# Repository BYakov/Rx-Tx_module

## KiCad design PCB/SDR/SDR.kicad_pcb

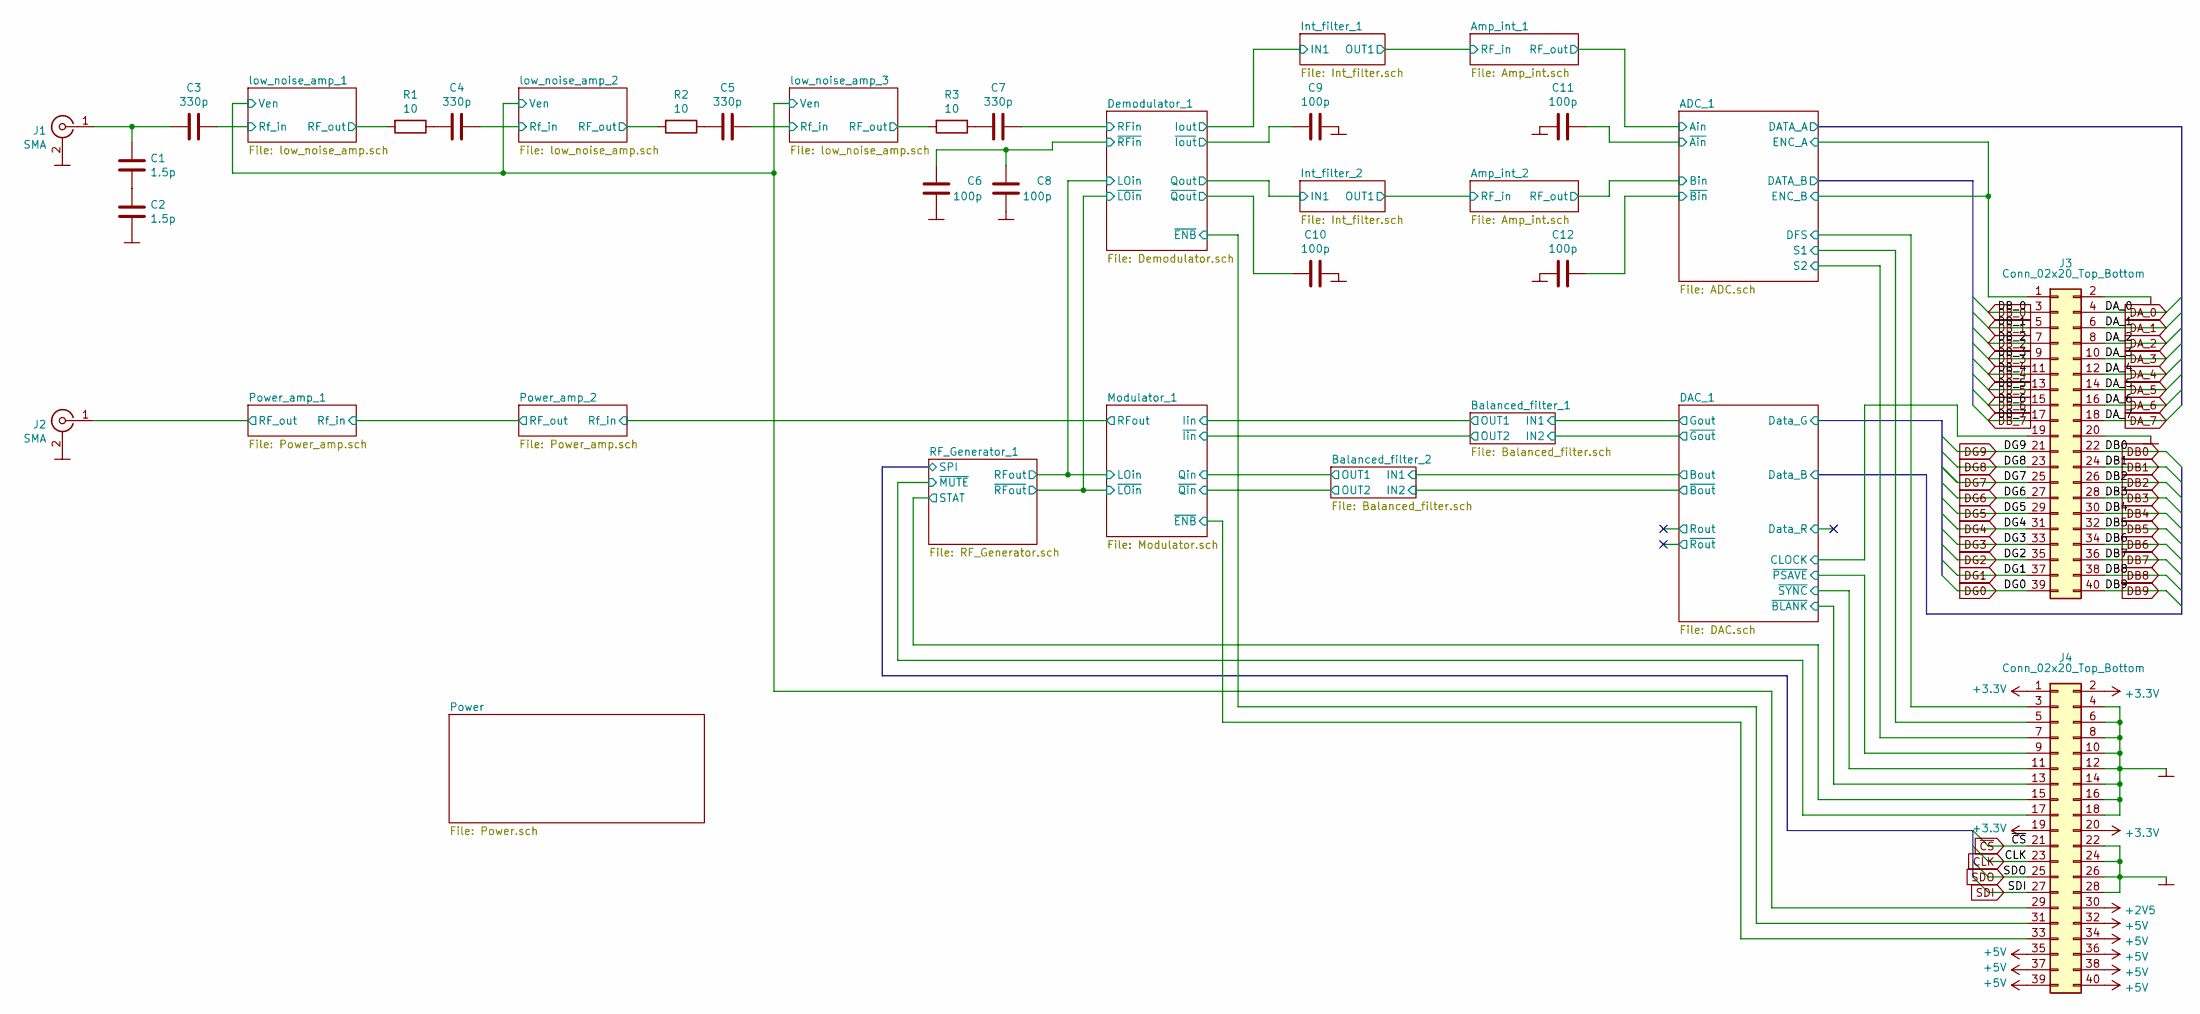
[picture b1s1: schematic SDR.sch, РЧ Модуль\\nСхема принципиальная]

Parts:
C1, C2: 1.5p; C_0805_2012Metric_Pad1.18x1.45mm_HandSolder
C3, C4, C5, C7: 330p; C_0805_2012Metric_Pad1.18x1.45mm_HandSolder
C6, C8, C9, C10, C11, C12: 100p; C_0805_2012Metric_Pad1.18x1.45mm_HandSolder
J1, J2: SMA; SMA_Amphenol_132289_EdgeMount
J3, J4: Conn_02x20_Top_Bottom; PinHeader_2x20_P2.54mm_Vertical
R1, R2, R3: 10; R_0805_2012Metric_Pad1.20x1.40mm_HandSolder

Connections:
+2V5: J4.30; also elsewhere on the board
+3V3: J4.1, J4.2, J4.19, J4.20; also elsewhere on the board
+5V: J4.32, J4.34, J4.35, J4.36, J4.37, J4.38, J4.39, J4.40; also elsewhere on the board
/ADC_1/DFS: J4.3; also elsewhere on the board
/ADC_1/ENC_A: J3.1; also elsewhere on the board
/ADC_1/S1: J4.5; also elsewhere on the board
/ADC_1/S2: J4.7; also elsewhere on the board
/ADC_1/~Ain: C12.2; also elsewhere on the board
/ADC_1/~Bin: C11.2; also elsewhere on the board
/DAC_1/CLOCK: J3.19; also elsewhere on the board
/DAC_1/~BLANK: J4.13; also elsewhere on the board
/DAC_1/~PSAVE: J4.9; also elsewhere on the board
/DAC_1/~SYNC: J4.11; also elsewhere on the board
/Demodulator_1/RFin: C7.1; also elsewhere on the board
/Demodulator_1/~ENB: J4.31; also elsewhere on the board
/Demodulator_1/~Iout: C9.1; also elsewhere on the board
/Demodulator_1/~Qout: C10.1; also elsewhere on the board
/Demodulator_1/~RFin: C6.2, C8.2; also elsewhere on the board
/Modulator_1/~ENB: J4.33; also elsewhere on the board
/Power_amp_1/RF_out: J2.1 (In); also elsewhere on the board
/RF_Generator_1/STAT: J4.15; also elsewhere on the board
/RF_Generator_1/~MUTE: J4.17; also elsewhere on the board
/low_noise_amp_1/RF_out: R1.2; also elsewhere on the board
/low_noise_amp_1/Rf_in: C3.1; also elsewhere on the board
/low_noise_amp_1/Ven: J4.29; also elsewhere on the board
/low_noise_amp_2/RF_out: R2.2; also elsewhere on the board
/low_noise_amp_2/Rf_in: C4.1; also elsewhere on the board
/low_noise_amp_3/RF_out: R3.2; also elsewhere on the board
/low_noise_amp_3/Rf_in: C5.1; also elsewhere on the board
CLK: J4.23; also elsewhere on the board
COMM: C2.2, C6.1, C8.1, C9.2, C10.2, C11.1, C12.1, J1.2 (Ext), J2.2 (Ext), J3.2, J3.20, J4.4, J4.6, J4.8, J4.10, J4.12, J4.14, J4.16, J4.18, J4.22, J4.24, J4.26, J4.28; also elsewhere on the board
DA_0: J3.4; also elsewhere on the board
DA_1: J3.6; also elsewhere on the board
DA_2: J3.8; also elsewhere on the board
DA_3: J3.10; also elsewhere on the board
DA_4: J3.12; also elsewhere on the board
DA_5: J3.14; also elsewhere on the board
DA_6: J3.16; also elsewhere on the board
DA_7: J3.18; also elsewhere on the board
DB0: J3.22; also elsewhere on the board
DB1: J3.24; also elsewhere on the board
DB2: J3.26; also elsewhere on the board
DB3: J3.28; also elsewhere on the board
DB4: J3.30; also elsewhere on the board
DB5: J3.32; also elsewhere on the board
DB6: J3.34; also elsewhere on the board
DB7: J3.36; also elsewhere on the board
DB8: J3.38; also elsewhere on the board
DB9: J3.40; also elsewhere on the board
DB_0: J3.3; also elsewhere on the board
DB_1: J3.5; also elsewhere on the board
DB_2: J3.7; also elsewhere on the board
DB_3: J3.9; also elsewhere on the board
DB_4: J3.11; also elsewhere on the board
DB_5: J3.13; also elsewhere on the board
DB_6: J3.15; also elsewhere on the board
DB_7: J3.17; also elsewhere on the board
DG0: J3.39; also elsewhere on the board
DG1: J3.37; also elsewhere on the board
DG2: J3.35; also elsewhere on the board
DG3: J3.33; also elsewhere on the board
DG4: J3.31; also elsewhere on the board
DG5: J3.29; also elsewhere on the board
DG6: J3.27; also elsewhere on the board
DG7: J3.25; also elsewhere on the board
DG8: J3.23; also elsewhere on the board
DG9: J3.21; also elsewhere on the board
unnamed: C1.1, C3.2, J1.1 (In)
unnamed: C1.2, C2.1
unnamed: C4.2, R1.1
unnamed: C5.2, R2.1
unnamed: C7.2, R3.1
SDI: J4.27; also elsewhere on the board
SDO: J4.25; also elsewhere on the board
~CS: J4.21; also elsewhere on the board

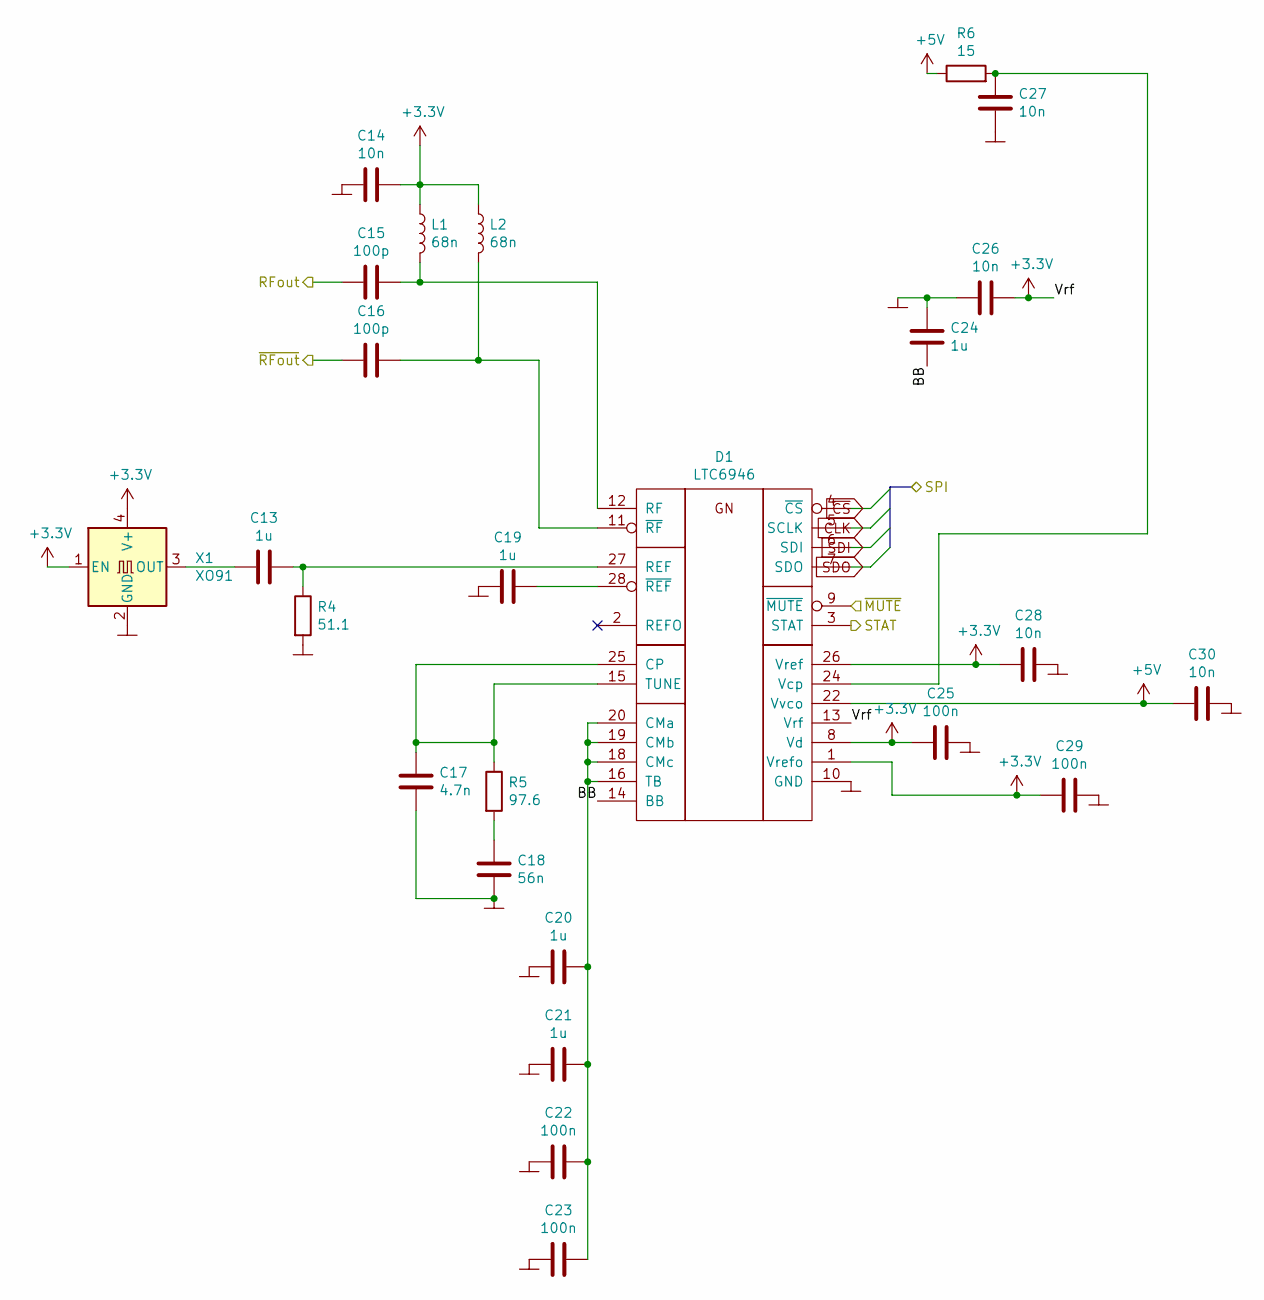
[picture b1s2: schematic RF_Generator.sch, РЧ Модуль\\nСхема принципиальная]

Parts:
C13, C19, C20, C21, C24: 1u; C_0805_2012Metric_Pad1.18x1.45mm_HandSolder
C14, C26, C27, C28, C30: 10n; C_1206_3216Metric_Pad1.33x1.80mm_HandSolder
C15, C16: 100p; C_0805_2012Metric_Pad1.18x1.45mm_HandSolder
C17: 4.7n; C_1206_3216Metric_Pad1.33x1.80mm_HandSolder
C18: 56n; C_1206_3216Metric_Pad1.33x1.80mm_HandSolder
C22, C23, C25, C29: 100n; C_1206_3216Metric_Pad1.33x1.80mm_HandSolder
D1: LTC6946; QFN-28-1EP_4x5mm_P0.5mm_EP2.65x3.65mm_ThermalVias
L1, L2: 68n; L_0402_1005Metric_Pad0.77x0.64mm_HandSolder
R4: 51.1; R_0805_2012Metric_Pad1.20x1.40mm_HandSolder
R5: 97.6; R_0805_2012Metric_Pad1.20x1.40mm_HandSolder
R6: 15; R_0805_2012Metric_Pad1.20x1.40mm_HandSolder
X1: XO91; Oscillator_SMD_EuroQuartz_XO91-4Pin_7.0x5.0mm

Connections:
+3V3: C14.1, C25.1, C26.1, C28.1, C29.1, D1.1 (Vrefo), D1.8 (Vd), D1.13 (Vrf), D1.26 (Vref), L1.1, L2.1, X1.1 (EN), X1.4 (V+); also elsewhere on the board
+5V: C30.1, D1.22 (Vvco), R6.1; also elsewhere on the board
/Demodulator_1/LOin: C15.2; also elsewhere on the board
/Demodulator_1/~LOin: C16.2; also elsewhere on the board
/RF_Generator_1/BB: C24.2, D1.14 (BB)
/RF_Generator_1/STAT: D1.3 (STAT); also elsewhere on the board
/RF_Generator_1/~MUTE: D1.9 (~MUTE); also elsewhere on the board
CLK: D1.5 (SCLK); also elsewhere on the board
COMM: C14.2, C17.2, C18.2, C19.1, C20.2, C21.2, C22.2, C23.2, C24.1, C25.2, C26.2, C27.2, C28.2, C29.2, C30.2, D1.10 (GND), D1.17 (GND), D1.21 (GND), D1.23 (GND), D1.29 (Ep), R4.2, X1.2 (GND); also elsewhere on the board
unnamed: C13.1, D1.27 (REF), R4.1
unnamed: C13.2, X1.3 (OUT)
unnamed: C15.1, D1.12 (RF), L1.2
unnamed: C16.1, D1.11 (~RF), L2.2
unnamed: C17.1, D1.15 (TUNE), D1.25 (CP), R5.1
unnamed: C18.1, R5.2
unnamed: C19.2, D1.28 (~REF)
unnamed: C20.1, C21.1, C22.1, C23.1, D1.16 (TB), D1.18 (CMc), D1.19 (CMb), D1.20 (CMa)
unnamed: C27.1, D1.24 (Vcp), R6.2
SDI: D1.6 (SDI); also elsewhere on the board
SDO: D1.7 (SDO); also elsewhere on the board
~CS: D1.4 (~CS); also elsewhere on the board

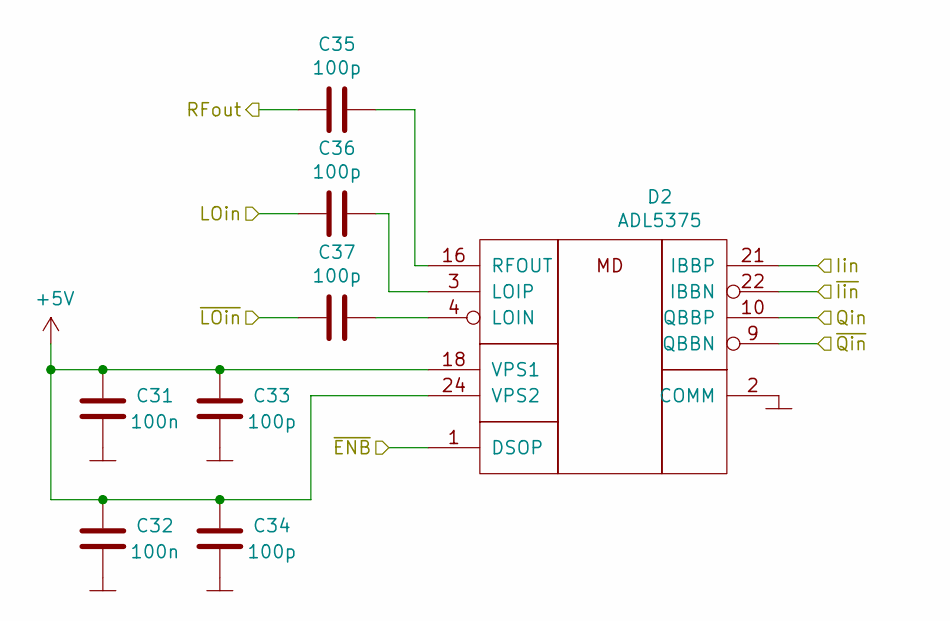
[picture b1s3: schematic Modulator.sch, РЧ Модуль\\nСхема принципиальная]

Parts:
C31, C32: 100n; C_1206_3216Metric_Pad1.33x1.80mm_HandSolder
C33, C34, C35, C36, C37: 100p; C_0805_2012Metric_Pad1.18x1.45mm_HandSolder
D2: ADL5375; LFCSP-24-1EP_4x4mm_P0.5mm_EP2.5x2.5mm_ThermalVias

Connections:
+5V: C31.2, C32.2, C33.2, C34.2, D2.18 (VPS1), D2.24 (VPS2); also elsewhere on the board
/Balanced_filter_1/OUT2: D2.22 (IBBN); also elsewhere on the board
/Balanced_filter_2/OUT1: D2.10 (QBBP); also elsewhere on the board
/Balanced_filter_2/OUT2: D2.9 (QBBN); also elsewhere on the board
/Demodulator_1/LOin: C36.2; also elsewhere on the board
/Demodulator_1/~LOin: C37.2; also elsewhere on the board
/Modulator_1/Iin: D2.21 (IBBP); also elsewhere on the board
/Modulator_1/RFout: C35.1; also elsewhere on the board
/Modulator_1/~ENB: D2.1 (DSOP); also elsewhere on the board
COMM: C31.1, C32.1, C33.1, C34.1, D2.2 (COMM), D2.5 (COMM), D2.8 (COMM), D2.11 (COMM), D2.12 (COMM), D2.14 (COMM), D2.17 (COMM), D2.19 (COMM), D2.20 (COMM), D2.23 (COMM), D2.25 (EP); also elsewhere on the board
unnamed: C35.2, D2.16 (RFOUT)
unnamed: C36.1, D2.3 (LOIP)
unnamed: C37.1, D2.4 (LOIN)

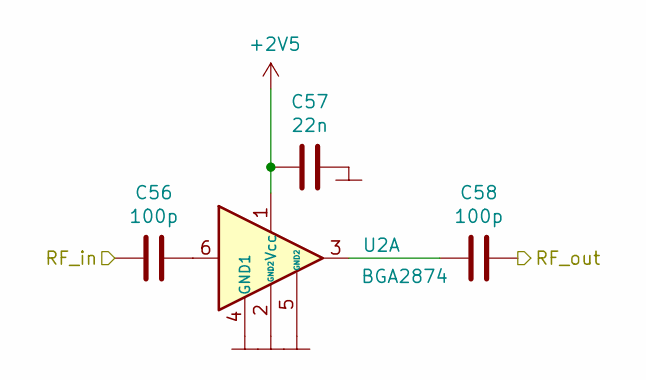
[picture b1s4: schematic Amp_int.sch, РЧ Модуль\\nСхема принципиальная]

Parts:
C38, C40: 100p; C_0805_2012Metric_Pad1.18x1.45mm_HandSolder
C39: 22n; C_0805_2012Metric_Pad1.18x1.45mm_HandSolder
U1: BGA2874; SOT-363_SC-70-6_Handsoldering

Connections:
+2V5: C39.2, U1.1 (Vcc); also elsewhere on the board
/ADC_1/Bin: C40.1; also elsewhere on the board
/Int_filter_1/OUT1: C38.2; also elsewhere on the board
COMM: C39.1, U1.2 (GND2), U1.4 (GND1), U1.5 (GND2); also elsewhere on the board
unnamed: C38.1, U1.6
unnamed: C40.2, U1.3

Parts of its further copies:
C56, C58: 100p; C_0805_2012Metric_Pad1.18x1.45mm_HandSolder
C57: 22n; C_0805_2012Metric_Pad1.18x1.45mm_HandSolder
U2: BGA2874; SOT-363_SC-70-6_Handsoldering

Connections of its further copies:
+2V5: C57.2, U2.1 (Vcc); also elsewhere on the board
/ADC_1/Ain: C58.1; also elsewhere on the board
/Int_filter_2/OUT1: C56.2; also elsewhere on the board
COMM: C57.1, U2.2 (GND2), U2.4 (GND1), U2.5 (GND2); also elsewhere on the board
unnamed: C56.1, U2.6
unnamed: C58.2, U2.3

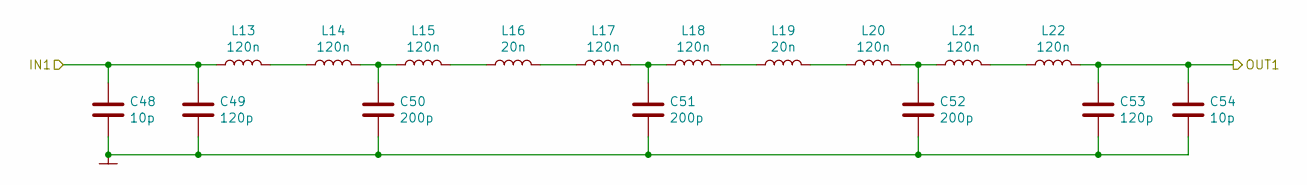
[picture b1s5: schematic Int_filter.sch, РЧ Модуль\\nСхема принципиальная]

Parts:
C41, C47: 10p; C_0805_2012Metric_Pad1.18x1.45mm_HandSolder
C42, C46: 120p; C_0805_2012Metric_Pad1.18x1.45mm_HandSolder
C43, C44, C45: 200p; C_0805_2012Metric_Pad1.18x1.45mm_HandSolder
L3, L4, L5, L7, L8, L10, L11, L12: 120n; L_0402_1005Metric_Pad0.77x0.64mm_HandSolder
L6, L9: 20n; L_0603_1608Metric_Pad1.05x0.95mm_HandSolder

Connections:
/Int_filter_1/IN1: C41.1, C42.1, L3.1; also elsewhere on the board
/Int_filter_1/OUT1: C46.1, C47.1, L12.2; also elsewhere on the board
COMM: C41.2, C42.2, C43.2, C44.2, C45.2, C46.2, C47.2; also elsewhere on the board
unnamed: C43.1, L4.2, L5.1
unnamed: C44.1, L7.2, L8.1
unnamed: C45.1, L10.2, L11.1
unnamed: L3.2, L4.1
unnamed: L5.2, L6.1
unnamed: L6.2, L7.1
unnamed: L8.2, L9.1
unnamed: L9.2, L10.1
unnamed: L11.2, L12.1

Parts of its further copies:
C48, C54: 10p; C_0805_2012Metric_Pad1.18x1.45mm_HandSolder
C49, C53: 120p; C_0805_2012Metric_Pad1.18x1.45mm_HandSolder
C50, C51, C52: 200p; C_0805_2012Metric_Pad1.18x1.45mm_HandSolder
L13, L14, L15, L17, L18, L20, L21, L22: 120n; L_0402_1005Metric_Pad0.77x0.64mm_HandSolder
L16, L19: 20n; L_0603_1608Metric_Pad1.05x0.95mm_HandSolder

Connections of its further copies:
/Int_filter_2/IN1: C48.1, C49.1, L13.1; also elsewhere on the board
/Int_filter_2/OUT1: C53.1, C54.1, L22.2; also elsewhere on the board
COMM: C48.2, C49.2, C50.2, C51.2, C52.2, C53.2, C54.2; also elsewhere on the board
unnamed: C50.1, L14.2, L15.1
unnamed: C51.1, L17.2, L18.1
unnamed: C52.1, L20.2, L21.1
unnamed: L13.2, L14.1
unnamed: L15.2, L16.1
unnamed: L16.2, L17.1
unnamed: L18.2, L19.1
unnamed: L19.2, L20.1
unnamed: L21.2, L22.1

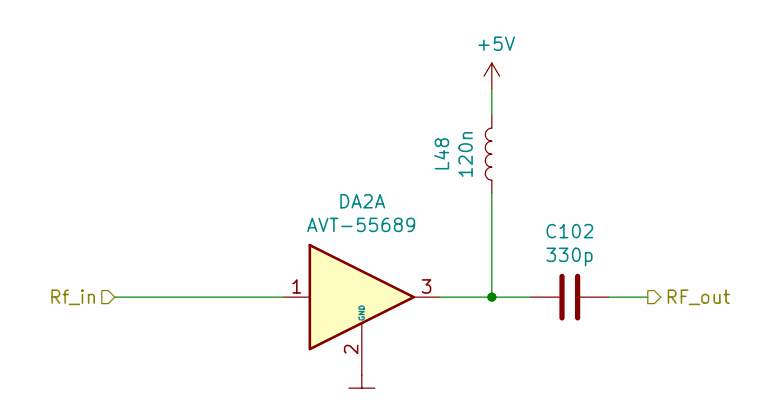
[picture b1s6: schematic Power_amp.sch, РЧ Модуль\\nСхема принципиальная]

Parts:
C55: 330p; C_1206_3216Metric_Pad1.33x1.80mm_HandSolder
DA1: AVT-55689; SOT-89-3_Handsoldering
L23: 120n; L_0402_1005Metric_Pad0.77x0.64mm_HandSolder

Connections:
+5V: L23.2; also elsewhere on the board
/Power_amp_1/RF_out: C55.1; also elsewhere on the board
/Power_amp_2/RF_out: DA1.1; also elsewhere on the board
COMM: DA1.2 (GND); also elsewhere on the board
unnamed: C55.2, DA1.3, L23.1

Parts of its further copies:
C102: 330p; C_1206_3216Metric_Pad1.33x1.80mm_HandSolder
DA2: AVT-55689; SOT-89-3_Handsoldering
L48: 120n; L_0402_1005Metric_Pad0.77x0.64mm_HandSolder

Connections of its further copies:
+5V: L48.2; also elsewhere on the board
/Modulator_1/RFout: DA2.1; also elsewhere on the board
/Power_amp_2/RF_out: C102.1; also elsewhere on the board
COMM: DA2.2 (GND); also elsewhere on the board
unnamed: C102.2, DA2.3, L48.1

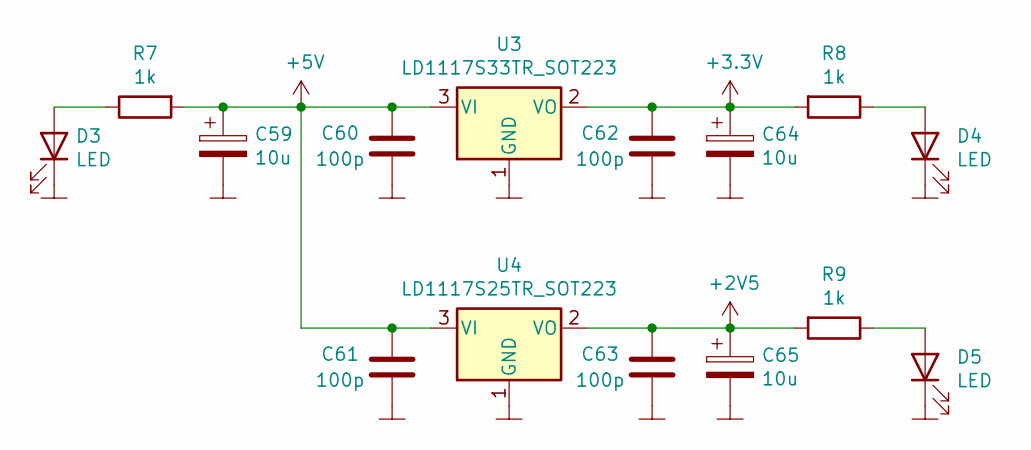
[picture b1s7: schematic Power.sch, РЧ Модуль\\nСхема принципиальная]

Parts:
C59, C64, C65: 10u; CP_Elec_4x5.4
C60, C61, C62, C63: 100p; C_0805_2012Metric_Pad1.18x1.45mm_HandSolder
D3, D4, D5: LED; D_1206_3216Metric_Pad1.42x1.75mm_HandSolder
R7, R8, R9: 1k; R_0805_2012Metric_Pad1.20x1.40mm_HandSolder
U3: LD1117S33TR_SOT223; SOT-223-3_TabPin2
U4: LD1117S25TR_SOT223; SOT-223-3_TabPin2

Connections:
+2V5: C63.2, C65.1, R9.2, U4.2 (VO); also elsewhere on the board
+3V3: C62.2, C64.1, R8.2, U3.2 (VO); also elsewhere on the board
+5V: C59.1, C60.2, C61.2, R7.2, U3.3 (VI), U4.3 (VI); also elsewhere on the board
COMM: C59.2, C60.1, C61.1, C62.1, C63.1, C64.2, C65.2, D3.1 (K), D4.1 (K), D5.1 (K), U3.1 (GND), U4.1 (GND); also elsewhere on the board
unnamed: D3.2 (A), R7.1
unnamed: D4.2 (A), R8.1
unnamed: D5.2 (A), R9.1

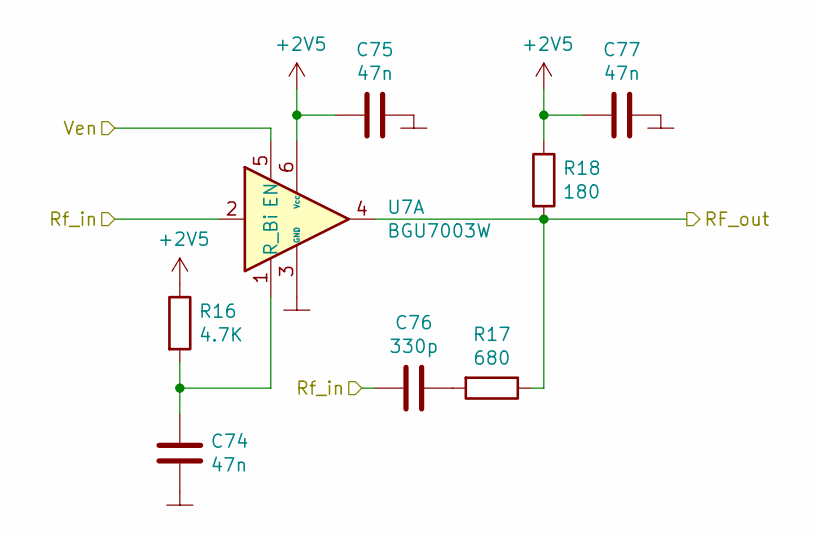
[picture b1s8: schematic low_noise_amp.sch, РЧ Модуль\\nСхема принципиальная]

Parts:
C66, C67, C69: 47n; C_1206_3216Metric_Pad1.33x1.80mm_HandSolder
C68: 330p; C_0805_2012Metric_Pad1.18x1.45mm_HandSolder
R10: 4.7К; R_0805_2012Metric_Pad1.20x1.40mm_HandSolder
R11: 680; R_0805_2012Metric_Pad1.20x1.40mm_HandSolder
R12: 180; R_0805_2012Metric_Pad1.20x1.40mm_HandSolder
U5: BGU7003W; SOT-886

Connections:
+2V5: C67.2, C69.2, R10.1, R12.1, U5.6 (Vcc); also elsewhere on the board
/low_noise_amp_1/RF_out: R11.1, R12.2, U5.4; also elsewhere on the board
/low_noise_amp_1/Rf_in: C68.2, U5.2; also elsewhere on the board
/low_noise_amp_1/Ven: U5.5 (EN); also elsewhere on the board
COMM: C66.2, C67.1, C69.1, U5.3 (GND); also elsewhere on the board
unnamed: C66.1, R10.2, U5.1 (R_Bi)
unnamed: C68.1, R11.2

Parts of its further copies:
C70, C71, C73, C74, C75, C77: 47n; C_1206_3216Metric_Pad1.33x1.80mm_HandSolder
C72, C76: 330p; C_0805_2012Metric_Pad1.18x1.45mm_HandSolder
R13, R16: 4.7К; R_0805_2012Metric_Pad1.20x1.40mm_HandSolder
R14, R17: 680; R_0805_2012Metric_Pad1.20x1.40mm_HandSolder
R15, R18: 180; R_0805_2012Metric_Pad1.20x1.40mm_HandSolder
U6, U7: BGU7003W; SOT-886

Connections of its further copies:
+2V5: C71.2, C73.2, C75.2, C77.2, R13.1, R15.1, R16.1, R18.1, U6.6 (Vcc), U7.6 (Vcc); also elsewhere on the board
/low_noise_amp_1/Ven: U6.5 (EN), U7.5 (EN); also elsewhere on the board
/low_noise_amp_2/RF_out: R14.1, R15.2, U6.4; also elsewhere on the board
/low_noise_amp_2/Rf_in: C72.2, U6.2; also elsewhere on the board
/low_noise_amp_3/RF_out: R17.1, R18.2, U7.4; also elsewhere on the board
/low_noise_amp_3/Rf_in: C76.2, U7.2; also elsewhere on the board
COMM: C70.2, C71.1, C73.1, C74.2, C75.1, C77.1, U6.3 (GND), U7.3 (GND); also elsewhere on the board
unnamed: C70.1, R13.2, U6.1 (R_Bi)
unnamed: C72.1, R14.2
unnamed: C74.1, R16.2, U7.1 (R_Bi)
unnamed: C76.1, R17.2

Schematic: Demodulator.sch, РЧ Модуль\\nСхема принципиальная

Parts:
C78, C79, C80: 100n; C_1206_3216Metric_Pad1.33x1.80mm_HandSolder
C81, C82, C83: 100p; C_0805_2012Metric_Pad1.18x1.45mm_HandSolder
D6: ADL5380; LFCSP-24-1EP_4x4mm_P0.5mm_EP2.5x2.5mm_ThermalVias
R19: R; R_0805_2012Metric_Pad1.20x1.40mm_HandSolder

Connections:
+5V: C78.2, C79.2, C80.2, C81.2, C82.2, C83.2, D6.6 (VCC1), D6.13 (VCC2), D6.24 (VCC3), R19.2; also elsewhere on the board
/Demodulator_1/LOin: D6.9 (LOIP); also elsewhere on the board
/Demodulator_1/RFin: D6.22 (RFIP); also elsewhere on the board
/Demodulator_1/~ENB: D6.7 (ENBL); also elsewhere on the board
/Demodulator_1/~Iout: D6.4 (ILO); also elsewhere on the board
/Demodulator_1/~LOin: D6.10 (LOIN); also elsewhere on the board
/Demodulator_1/~Qout: D6.16 (QLO); also elsewhere on the board
/Demodulator_1/~RFin: D6.21 (RFIN); also elsewhere on the board
/Int_filter_1/IN1: D6.3 (IHI); also elsewhere on the board
/Int_filter_2/IN1: D6.15 (QHI); also elsewhere on the board
COMM: C78.1, C79.1, C80.1, C81.1, C82.1, C83.1, D6.1 (GND3), D6.2 (GND1), D6.5 (GND1), D6.8 (GND4), D6.11 (GND4), D6.14 (GND2), D6.17 (GND2), D6.18 (GND3), D6.20 (GND3), D6.23 (GND3), D6.25 (EP); also elsewhere on the board
unnamed: D6.19 (ADJ), R19.1

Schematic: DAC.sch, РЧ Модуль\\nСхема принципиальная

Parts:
C84: 1u; C_1206_3216Metric_Pad1.33x1.80mm_HandSolder
C85, C86, C87: 100n; C_1206_3216Metric_Pad1.33x1.80mm_HandSolder
D7: ADV7123; LQFP-48_7x7mm_P0.5mm
D8: D_Zener; SOT-23
R20: R; R_0805_2012Metric_Pad1.20x1.40mm_HandSolder
R21: 1.5k; R_0805_2012Metric_Pad1.20x1.40mm_HandSolder

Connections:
+3V3: C85.1, C86.2, C87.1, D7.13 (VAA), D7.29 (VAA), D7.30 (VAA), R21.1; also elsewhere on the board
/Balanced_filter_1/IN2: D7.31 (~IOG); also elsewhere on the board
/Balanced_filter_2/IN2: D7.27 (~IOB); also elsewhere on the board
/DAC_1/Bout: D7.28 (IOB); also elsewhere on the board
/DAC_1/CLOCK: D7.24 (CLOCK); also elsewhere on the board
/DAC_1/DR0: D7.39 (R0)
/DAC_1/DR1: D7.40 (R1)
/DAC_1/DR2: D7.41 (R2)
/DAC_1/DR3: D7.42 (R3)
/DAC_1/DR4: D7.43 (R4)
/DAC_1/DR5: D7.44 (R5)
/DAC_1/DR6: D7.45 (R6)
/DAC_1/DR7: D7.46 (R7)
/DAC_1/DR8: D7.47 (R8)
/DAC_1/DR9: D7.48 (R9)
/DAC_1/Gout: D7.32 (IOG); also elsewhere on the board
/DAC_1/Rout: D7.34 (IOR)
/DAC_1/~BLANK: D7.11 (~BLANK); also elsewhere on the board
/DAC_1/~PSAVE: D7.38 (~PSAVE); also elsewhere on the board
/DAC_1/~Rout: D7.33 (~IOR)
/DAC_1/~SYNC: D7.12 (~SYNC); also elsewhere on the board
COMM: C84.2, C85.2, C87.2, D7.25 (GND), D7.26 (GND), D8.2 (A), R20.2; also elsewhere on the board
DB0: D7.14 (B0); also elsewhere on the board
DB1: D7.15 (B1); also elsewhere on the board
DB2: D7.16 (B2); also elsewhere on the board
DB3: D7.17 (B3); also elsewhere on the board
DB4: D7.18 (B4); also elsewhere on the board
DB5: D7.19 (B5); also elsewhere on the board
DB6: D7.20 (B6); also elsewhere on the board
DB7: D7.21 (B7); also elsewhere on the board
DB8: D7.22 (B8); also elsewhere on the board
DB9: D7.23 (B9); also elsewhere on the board
DG0: D7.1 (G0); also elsewhere on the board
DG1: D7.2 (G1); also elsewhere on the board
DG2: D7.3 (G2); also elsewhere on the board
DG3: D7.4 (G3); also elsewhere on the board
DG4: D7.5 (G4); also elsewhere on the board
DG5: D7.6 (G5); also elsewhere on the board
DG6: D7.7 (G6); also elsewhere on the board
DG7: D7.8 (G7); also elsewhere on the board
DG8: D7.9 (G8); also elsewhere on the board
DG9: D7.10 (G9); also elsewhere on the board
unnamed: C84.1, D7.36 (Vref), D8.1 (K), R21.2
unnamed: C86.1, D7.35 (COMP)
unnamed: D7.37 (Rset), R20.1

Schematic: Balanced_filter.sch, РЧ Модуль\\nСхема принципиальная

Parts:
C88, C94: 10p; C_0805_2012Metric_Pad1.18x1.45mm_HandSolder
C89, C93: 120p; C_0805_2012Metric_Pad1.18x1.45mm_HandSolder
C90, C91, C92: 200p; C_0805_2012Metric_Pad1.18x1.45mm_HandSolder
L24, L25, L26, L27, L32, L33, L34, L35: 120n; L_0402_1005Metric_Pad0.77x0.64mm_HandSolder
L28, L29, L30, L31: 10n; L_0402_1005Metric_Pad0.77x0.64mm_HandSolder

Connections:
/Balanced_filter_1/IN2: C88.2, C89.2, L25.1; also elsewhere on the board
/Balanced_filter_1/OUT2: C93.2, C94.2, L35.2; also elsewhere on the board
/DAC_1/Gout: C88.1, C89.1, L24.1; also elsewhere on the board
/Modulator_1/Iin: C93.1, C94.1, L34.2; also elsewhere on the board
unnamed: C90.1, L24.2, L26.1
unnamed: C90.2, L25.2, L27.1
unnamed: C91.1, L28.2, L30.1
unnamed: C91.2, L29.2, L31.1
unnamed: C92.1, L32.2, L34.1
unnamed: C92.2, L33.2, L35.1
unnamed: L26.2, L28.1
unnamed: L27.2, L29.1
unnamed: L30.2, L32.1
unnamed: L31.2, L33.1

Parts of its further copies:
C95, C101: 10p; C_0805_2012Metric_Pad1.18x1.45mm_HandSolder
C96, C100: 120p; C_0805_2012Metric_Pad1.18x1.45mm_HandSolder
C97, C98, C99: 200p; C_0805_2012Metric_Pad1.18x1.45mm_HandSolder
L36, L37, L38, L39, L44, L45, L46, L47: 120n; L_0402_1005Metric_Pad0.77x0.64mm_HandSolder
L40, L41, L42, L43: 10n; L_0402_1005Metric_Pad0.77x0.64mm_HandSolder

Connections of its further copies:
/Balanced_filter_2/IN2: C95.2, C96.2, L37.1; also elsewhere on the board
/Balanced_filter_2/OUT1: C100.1, C101.1, L46.2; also elsewhere on the board
/Balanced_filter_2/OUT2: C100.2, C101.2, L47.2; also elsewhere on the board
/DAC_1/Bout: C95.1, C96.1, L36.1; also elsewhere on the board
unnamed: C97.1, L36.2, L38.1
unnamed: C97.2, L37.2, L39.1
unnamed: C98.1, L40.2, L42.1
unnamed: C98.2, L41.2, L43.1
unnamed: C99.1, L44.2, L46.1
unnamed: C99.2, L45.2, L47.1
unnamed: L38.2, L40.1
unnamed: L39.2, L41.1
unnamed: L42.2, L44.1
unnamed: L43.2, L45.1

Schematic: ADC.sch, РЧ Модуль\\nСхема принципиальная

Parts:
C103, C104, C105, C106, C107, C108, C109, C110, C111: 100n; C_1206_3216Metric_Pad1.33x1.80mm_HandSolder
D9: AD9288; LQFP-48_7x7mm_P0.5mm

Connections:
+3V3: C103.2, C104.2, C105.2, C107.2, C108.2, C110.2, C111.2, D9.13 (VD), D9.15 (VDD), D9.28 (VDD), D9.30 (VD), D9.31 (VD), D9.33 (VDD), D9.46 (VDD), D9.48 (VD); also elsewhere on the board
/ADC_1/Ain: D9.2 (AinA); also elsewhere on the board
/ADC_1/Bin: D9.11 (AinB); also elsewhere on the board
/ADC_1/DFS: D9.4 (DFS); also elsewhere on the board
/ADC_1/ENC_A: D9.14 (ENCB), D9.47 (ENCA); also elsewhere on the board
/ADC_1/S1: D9.8 (S1); also elsewhere on the board
/ADC_1/S2: D9.9 (S2); also elsewhere on the board
/ADC_1/~Ain: D9.3 (~AinA); also elsewhere on the board
/ADC_1/~Bin: D9.10 (~AinB); also elsewhere on the board
COMM: C103.1, C104.1, C105.1, C106.2, C107.1, C108.1, C109.2, C110.1, C111.1, D9.1 (GND), D9.12 (GND), D9.16 (GND), D9.27 (GND), D9.29 (GND), D9.32 (GND), D9.34 (GND), D9.45 (GND); also elsewhere on the board
DA_0: D9.37 (D0A); also elsewhere on the board
DA_1: D9.38 (D1A); also elsewhere on the board
DA_2: D9.39 (D2A); also elsewhere on the board
DA_3: D9.40 (D3A); also elsewhere on the board
DA_4: D9.41 (D4A); also elsewhere on the board
DA_5: D9.42 (D5A); also elsewhere on the board
DA_6: D9.43 (D6A); also elsewhere on the board
DA_7: D9.44 (D7A); also elsewhere on the board
DB_0: D9.24 (D0B); also elsewhere on the board
DB_1: D9.23 (D1B); also elsewhere on the board
DB_2: D9.22 (D2B); also elsewhere on the board
DB_3: D9.21 (D3B); also elsewhere on the board
DB_4: D9.20 (D4B); also elsewhere on the board
DB_5: D9.19 (D5B); also elsewhere on the board
DB_6: D9.18 (D6B); also elsewhere on the board
DB_7: D9.17 (D7B); also elsewhere on the board
unnamed: C106.1, C109.1, D9.5 (REFA), D9.6 (REFout), D9.7 (REFB)

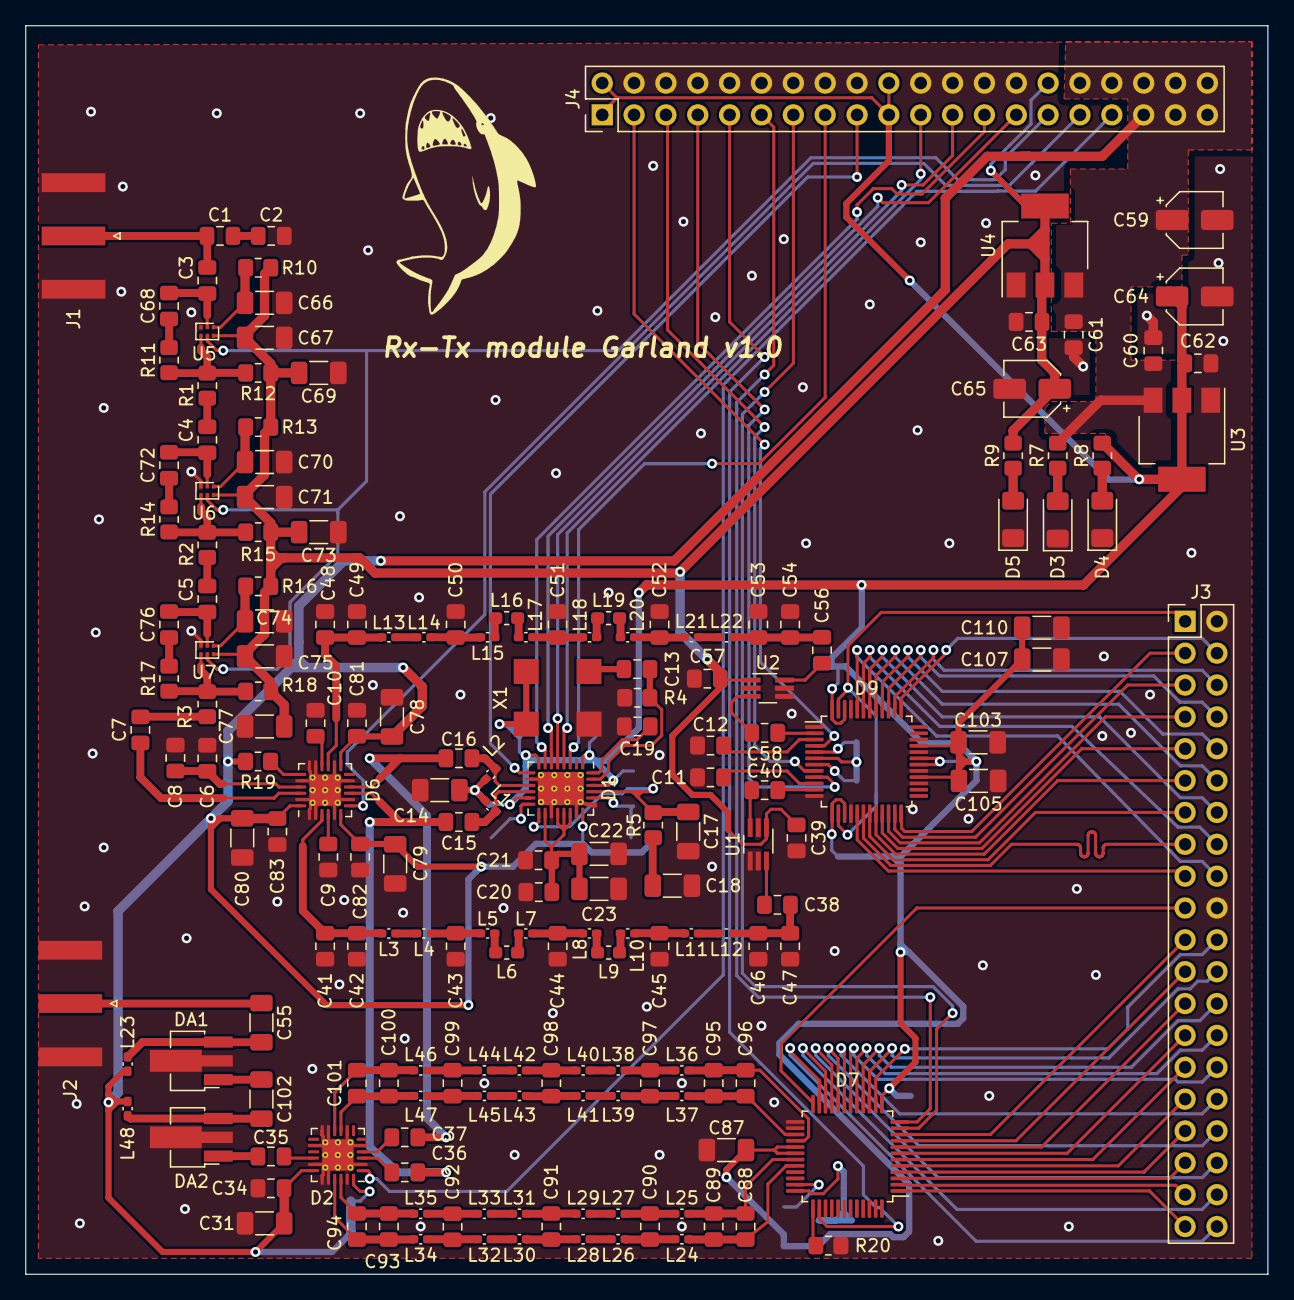
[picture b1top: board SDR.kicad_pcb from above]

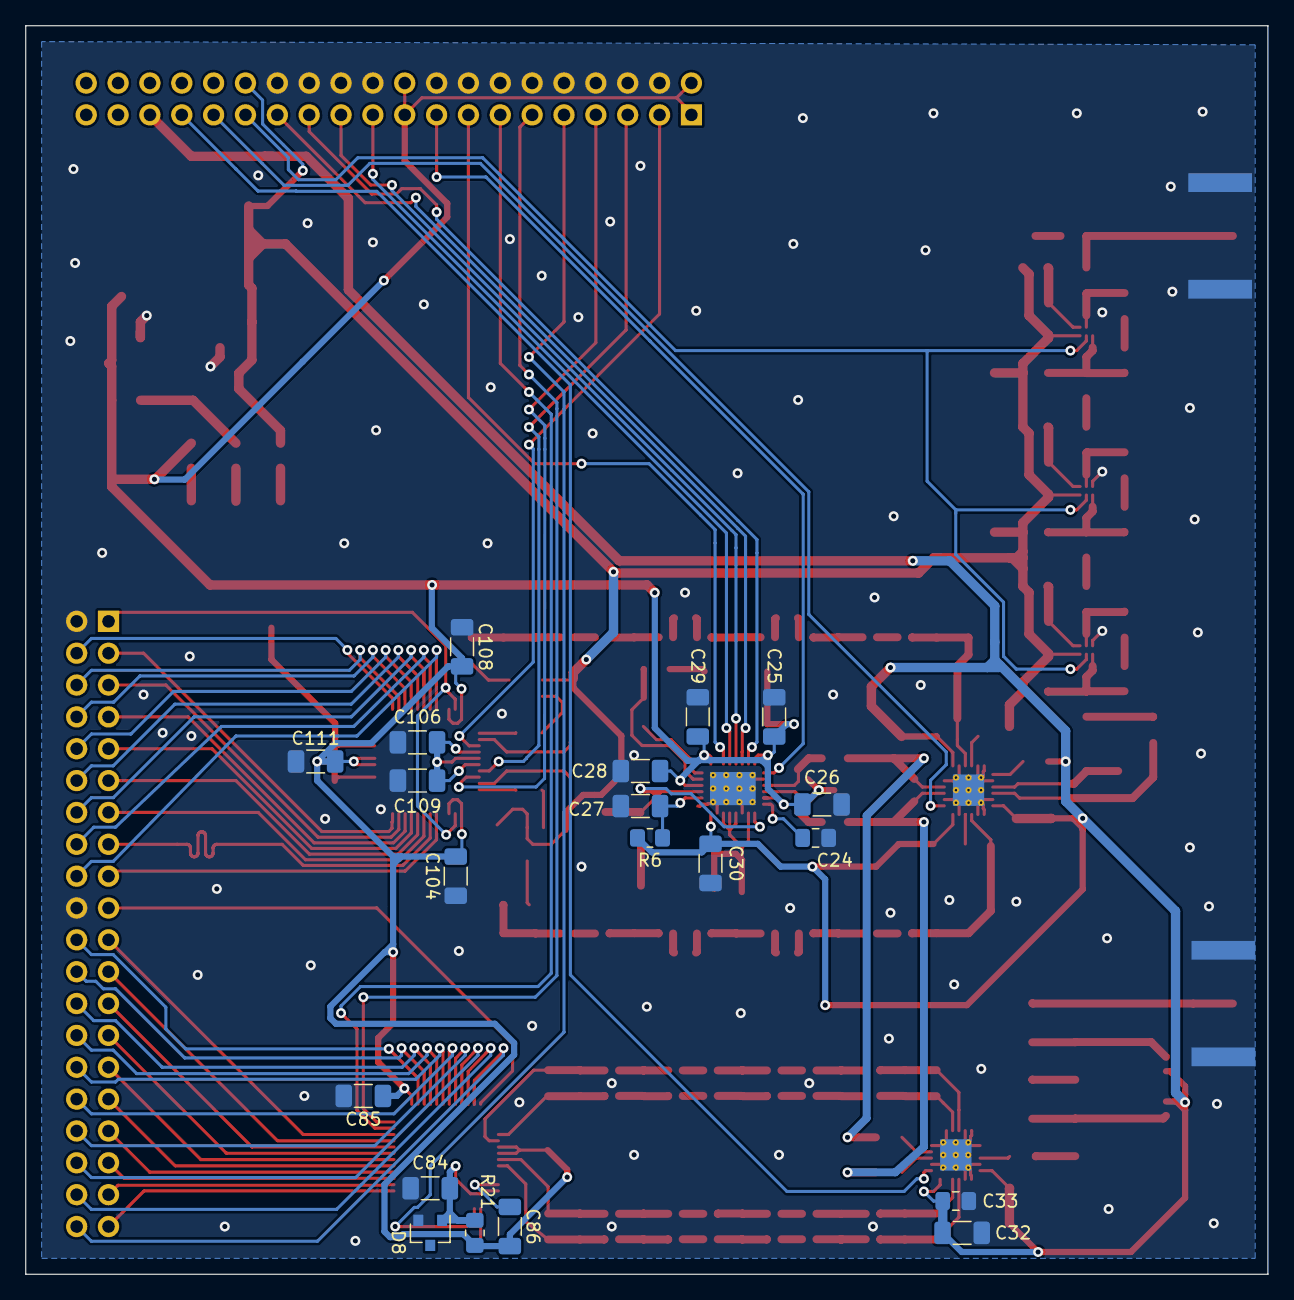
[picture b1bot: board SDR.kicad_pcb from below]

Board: 2 copper layers, 99.1 x 99.6 mm, 203 parts (20 on the bottom side), 164 nets.

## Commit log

2020-12-24 Kursach_7_smart
